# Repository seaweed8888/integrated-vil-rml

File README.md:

# Integrated VIL and RML
Integrated VIL and RML for the USC FSAE Formula Electric team I made. Has both VIL and RML functionality with galvanic isolation and all that. Fully compliant with FSAE rules

Working Ngspice sim with the schematic and pcb layout. Ready to Print

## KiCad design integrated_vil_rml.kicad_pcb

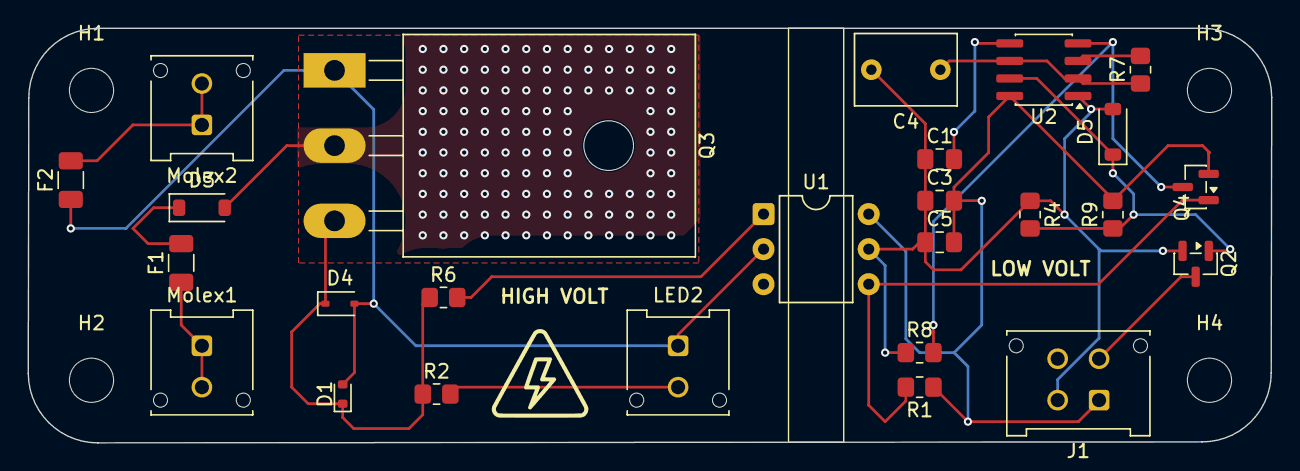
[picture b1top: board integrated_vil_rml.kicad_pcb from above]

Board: 2 copper layers, 90.1 x 30.0 mm, 30 parts (0 on the bottom side), 17 nets.

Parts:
C1: 0.1uF; C_0805_2012Metric_Pad1.18x1.45mm_HandSolder
C3: 1uF; C_0805_2012Metric_Pad1.18x1.45mm_HandSolder
C4: 1u; C_Rect_L7.2mm_W5.0mm_P5.00mm
C5: 100nF; C_0805_2012Metric_Pad1.18x1.45mm_HandSolder
D1: 1N4148WT-7; D_SOD-523
D3: BZT52C51-7-F; D_SOD-123
D4: PESD12VL1BA; D_SOD-323
D5: BZT52C8V2; D_SOD-123
F1, F2: 750mA; Fuse_1206_3216Metric
H1, H2, H3, H4: MountingHole; MountingHole_3.2mm_M3
J1: 043045-0412; Molex_Micro-Fit_3.0_43045-0412_2x02_P3.00mm_Vertical
LED2: Molex_Micro-Fit_3.0_43045-0212_2x01_P3.00mm_Vertical
Molex1, Molex2: 043045-0212; Molex_Micro-Fit_3.0_43045-0212_2x01_P3.00mm_Vertical
Q2: AO3400A; SOT-23
Q3: UJ3N065080K3S; TO-247-3_Horizontal_TabDown
Q4: AO3401A; SOT-23
R1: 2k; R_0805_2012Metric_Pad1.20x1.40mm_HandSolder
R2: 2200; R_0805_2012Metric_Pad1.20x1.40mm_HandSolder
R4: 100k; R_0805_2012Metric_Pad1.20x1.40mm_HandSolder
R6: 4.3k; R_0805_2012Metric_Pad1.20x1.40mm_HandSolder
R7: 750k; R_0805_2012Metric_Pad1.20x1.40mm_HandSolder
R8: 1k; R_0805_2012Metric_Pad1.20x1.40mm_HandSolder
R9: 10k; R_0805_2012Metric_Pad1.20x1.40mm_HandSolder
U1: H11L1; DIP-6_W7.62mm
U2: NE555; SOIC-8_3.9x4.9mm_P1.27mm

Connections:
/HV+: F1.1, Molex1.1, Molex1.2
/HV-: D1.2 (A), D4.2 (A2), F2.1, LED2.1, Q3.1 (G), U1.2
GLV+: C3.2, C5.2, J1.1, Q4.2 (S), R1.1, R9.2, U1.6, U2.8 (VCC)
GND: C1.1, C3.1, C4.2, C5.1, D5.2 (A), J1.2, Q2.2 (S), R4.1, R8.1, U1.5, U2.1 (GND)
LED_RETURN: J1.3, Q2.3 (D)
unnamed: D1.1 (K), D4.1 (A1), Q3.3 (S), R2.1, R6.1
unnamed: D3.2 (A), Q3.2 (D)
unnamed: D3.1 (K), F1.2
unnamed: D5.1 (K), Q2.1 (G), R4.2, R9.1, U2.7 (DIS)
unnamed: LED2.2, R2.2
unnamed: F2.2, Molex2.1, Molex2.2
unnamed: Q4.3 (D), R8.2, U2.4 (R)
unnamed: Q4.1 (G), R1.2, U1.4
unnamed: R6.2, U1.1
unnamed: C1.2, U2.5 (CV)
unnamed: R7.2, U2.3 (Q)
unnamed: C4.1, R7.1, U2.2 (TR), U2.6 (THR)
